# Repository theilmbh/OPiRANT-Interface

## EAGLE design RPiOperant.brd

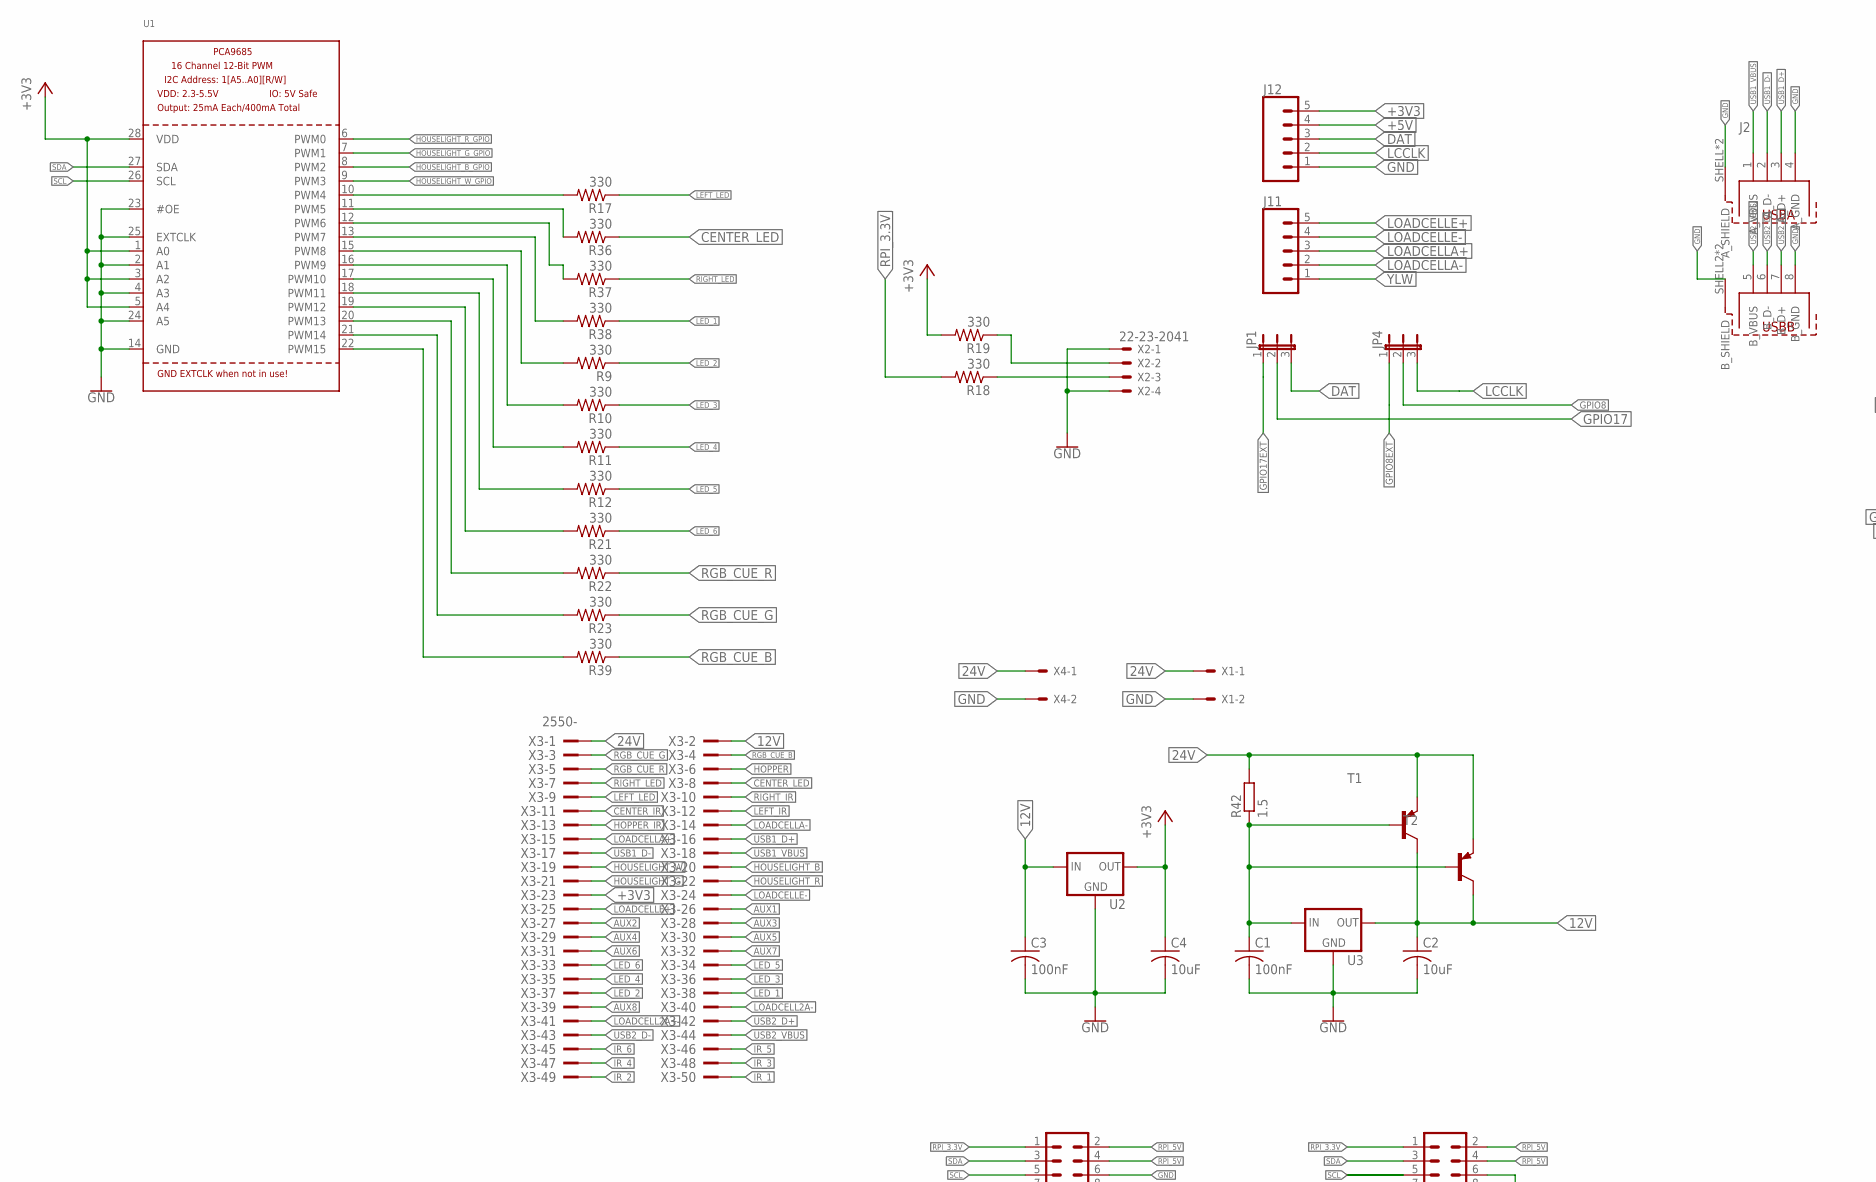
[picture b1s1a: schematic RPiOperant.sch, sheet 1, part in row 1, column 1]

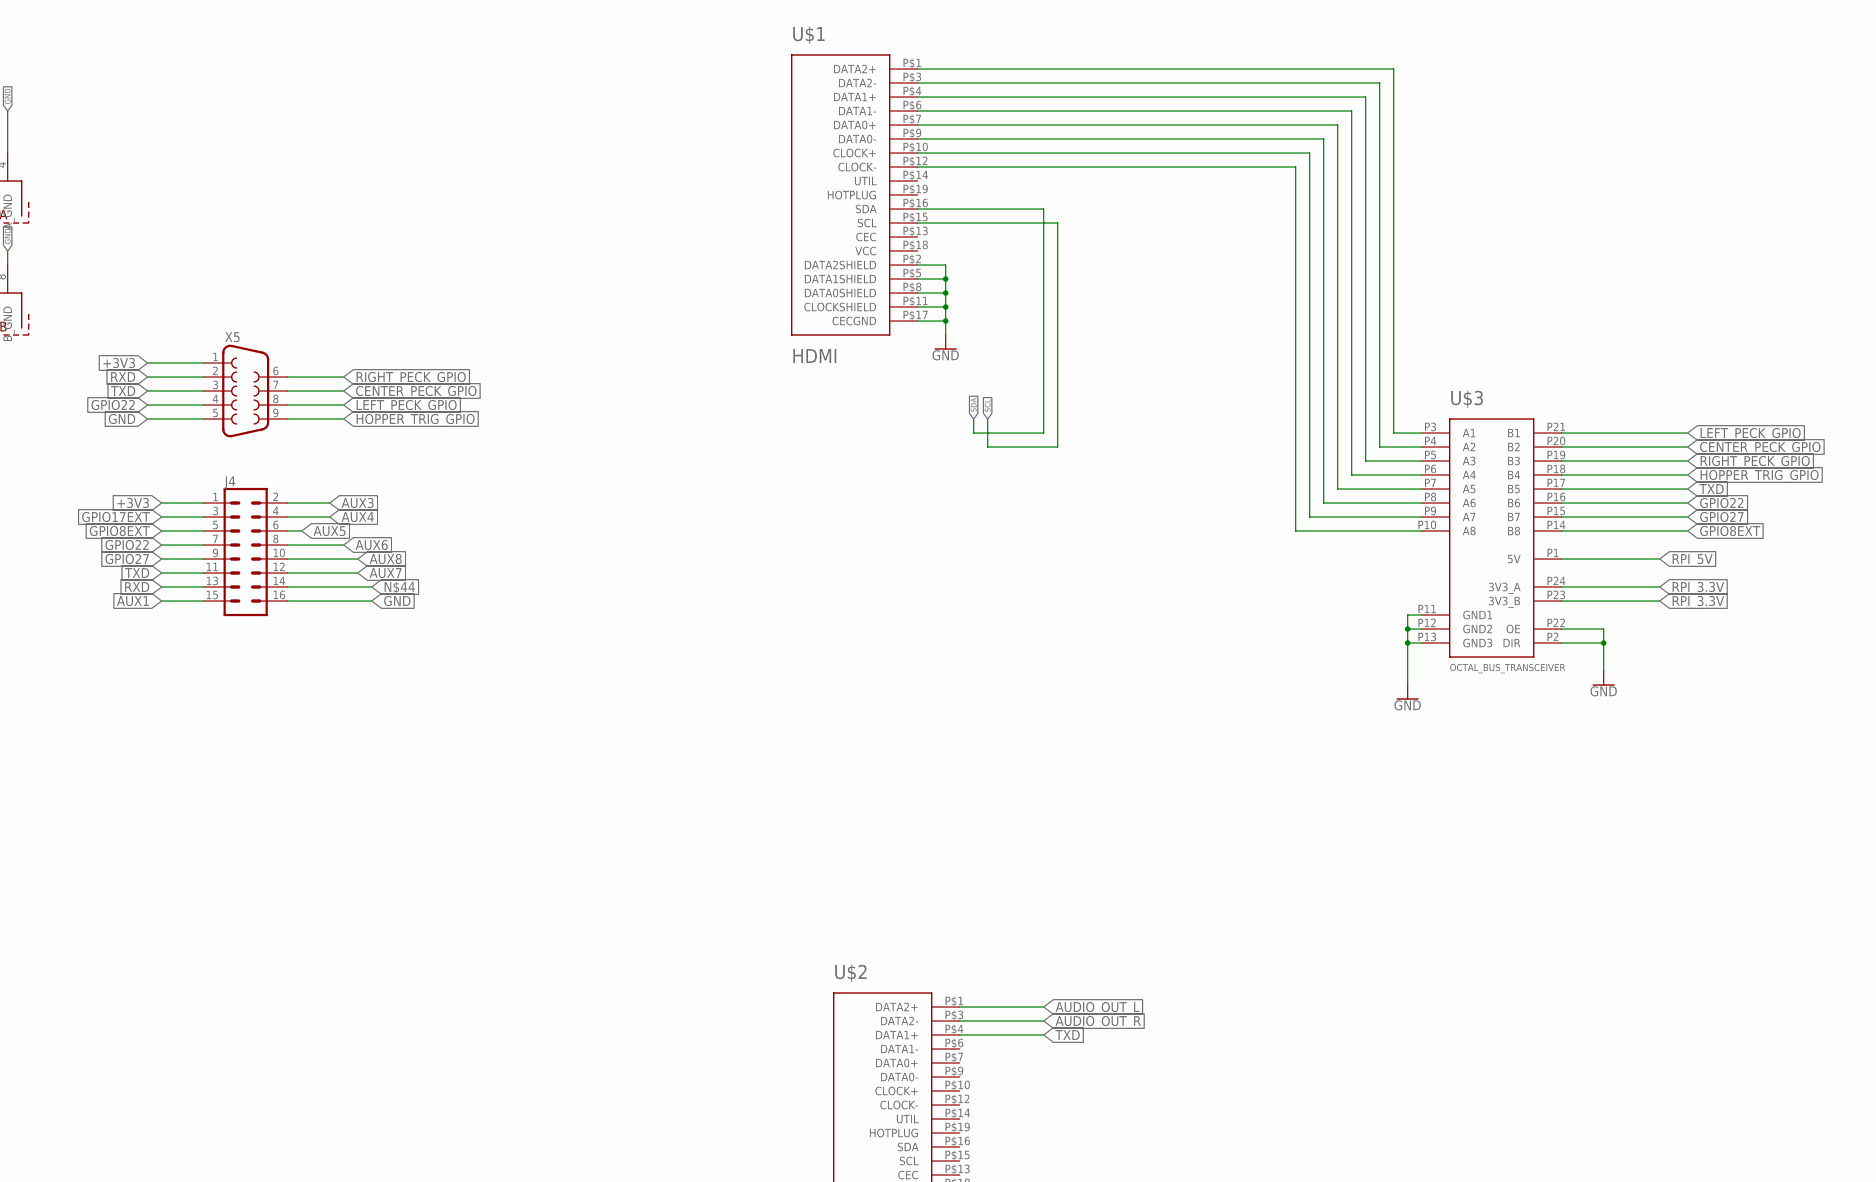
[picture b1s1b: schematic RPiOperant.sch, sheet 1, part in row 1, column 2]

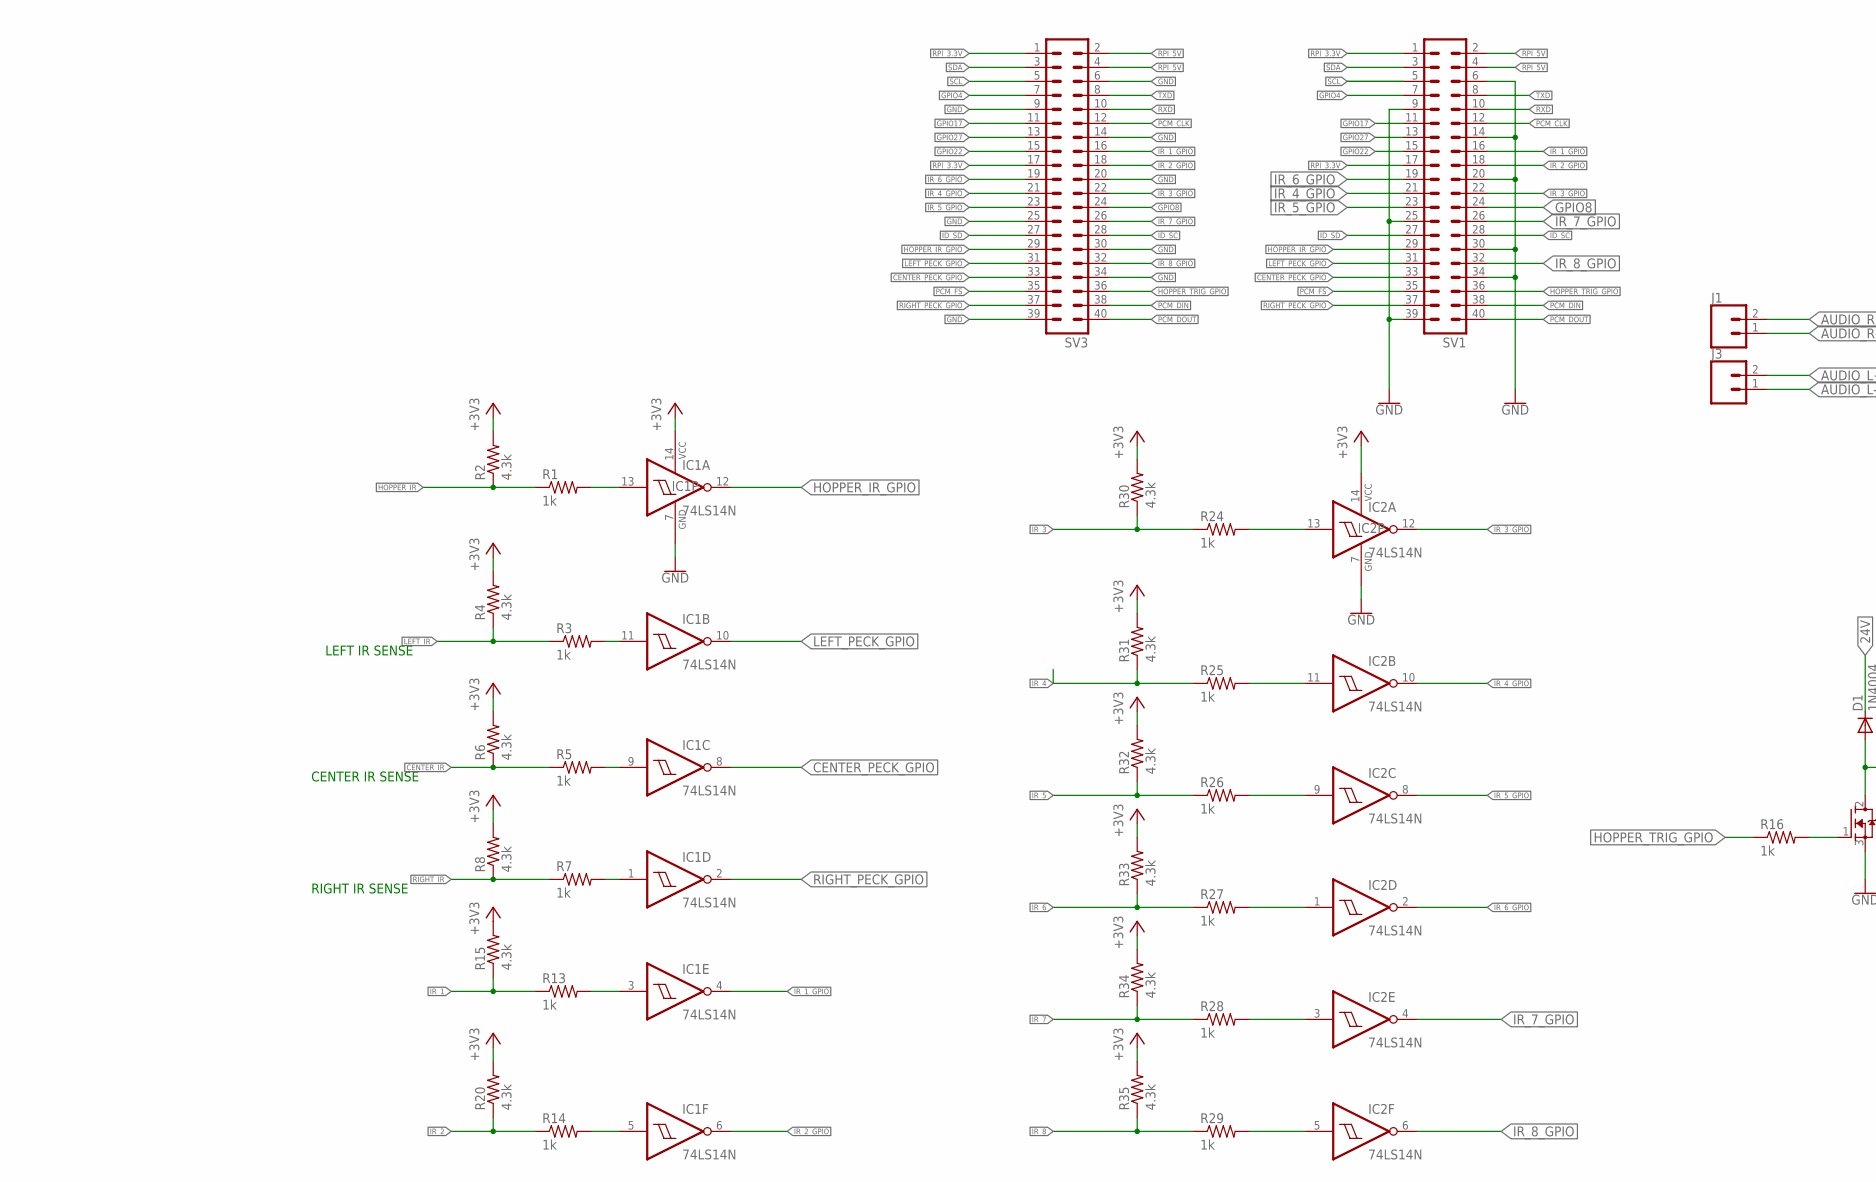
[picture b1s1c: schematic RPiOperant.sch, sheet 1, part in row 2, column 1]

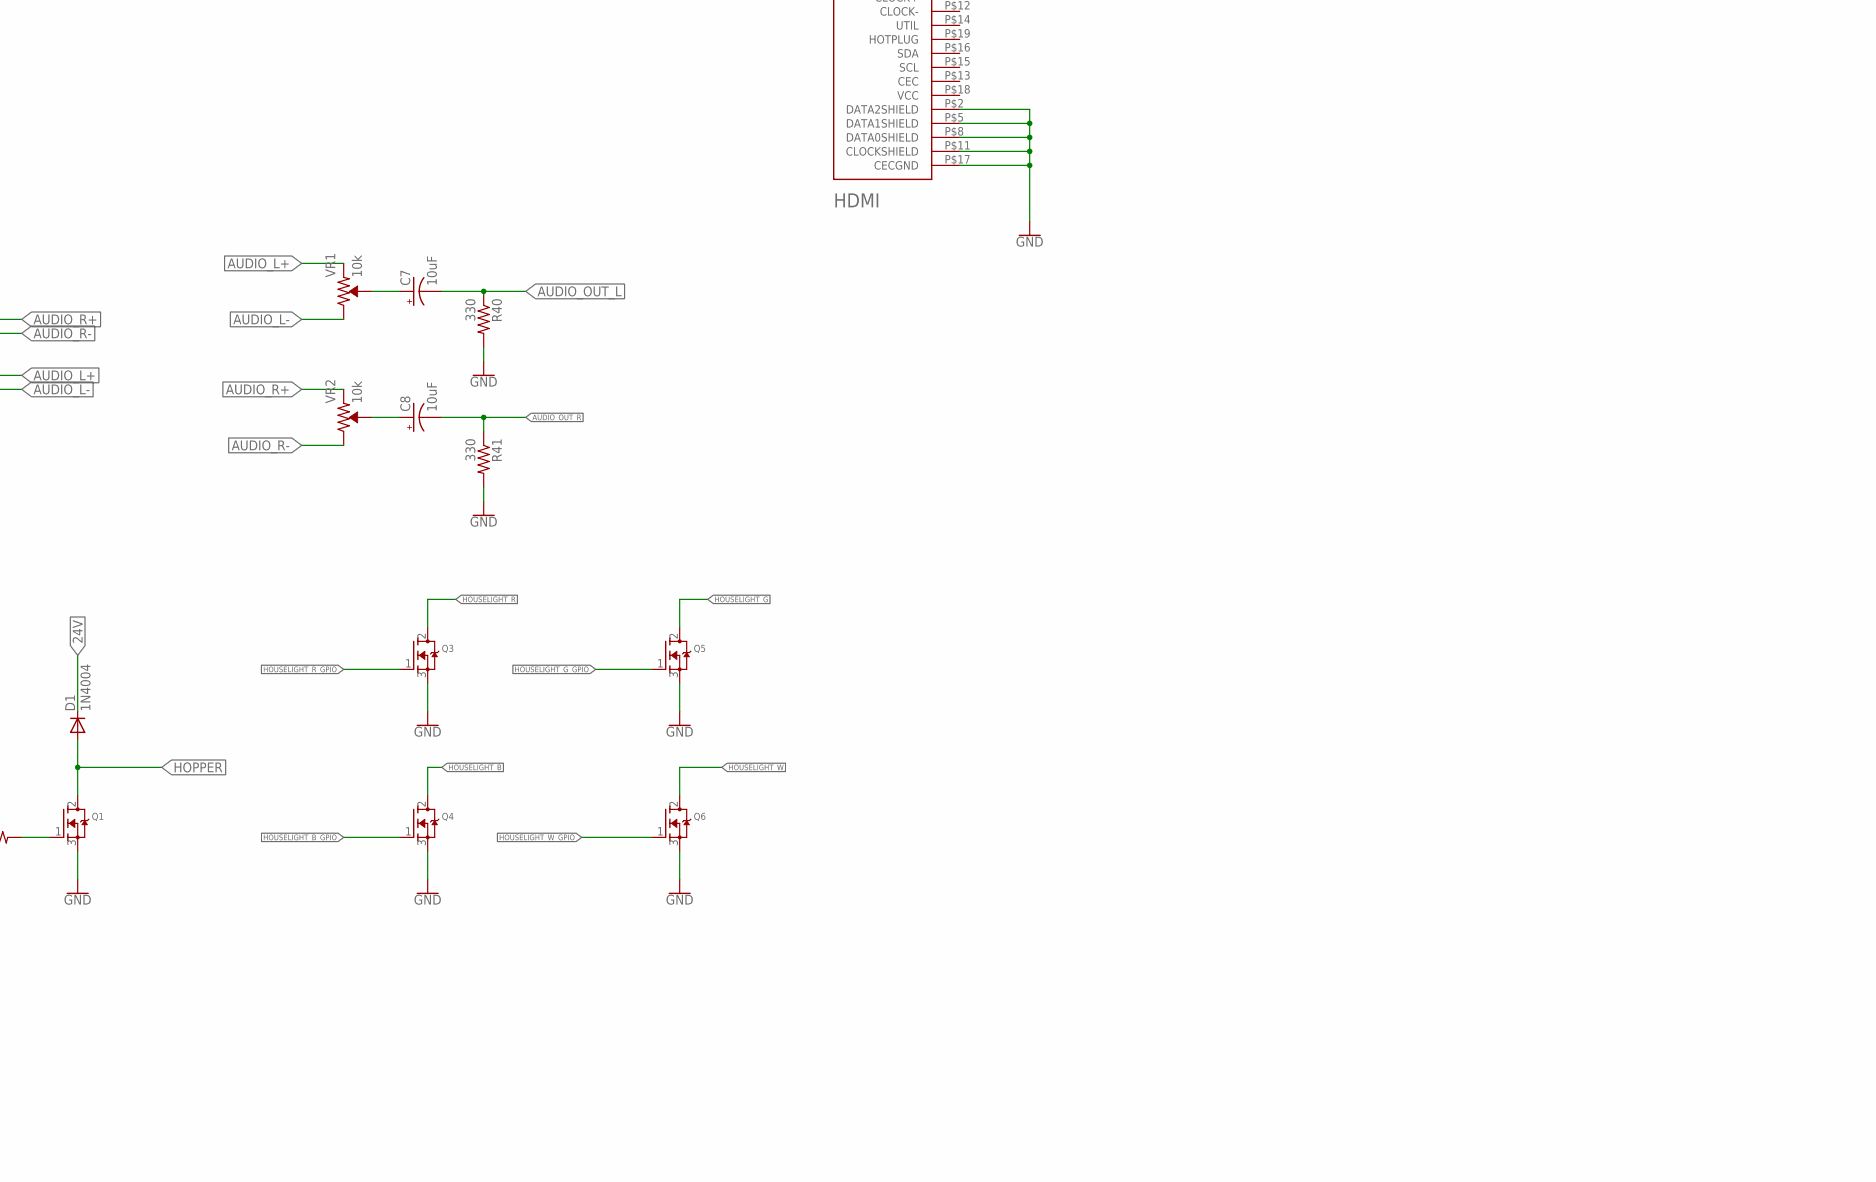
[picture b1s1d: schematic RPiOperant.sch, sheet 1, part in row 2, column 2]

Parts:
C1, C3: 100nF; C050-025X075
C2, C4: 10uF; C050-025X075
C7, C8: 10uF; CPOL-RADIAL-2.5MM-5MM
D1: 1N4004; DO41-10
IC1, IC2: 74LS14N; DIL14
J1, J3: CONN_02POLAR_LOCK; MOLEX-1X2_LOCK
J2: 61400826021
J4: CONN_08X2; 2X8
J11, J12: CONN_05; 1X05
JP1, JP4: JP2E; JP2
Q1, Q3, Q4, Q5, Q6: MOSFET-NGDS_TO220V; TO220V
R1, R3, R5, R7, R13, R14, R16, R24, R25, R26, R27, R28, R29: 1k; 0207/7
R2, R4, R6, R8, R15, R20, R30, R31, R32, R33, R34, R35: 4.3k; 0207/7
R9, R10, R11, R12, R17, R18, R19, R21, R22, R23, R36, R37, R38, R39, R40, R41: 330; 0207/7
R42: 1.5; 0411/15
SV1, SV3: MA20-2
T1, T2: -PNP-TO220V; TO220V
U1: PCA9685; TSSOP28
U2, U3: V_REG_78XXSINK; TO220-IGO
U$1, U$2: HDMI; HDMI_A
U$3: OCTAL_BUS_TRANSCEIVER; TSSOP-24
VR1, VR2: 10k; TRIMPOT-PTH-3386U
X1, X4: KK-156-2
X2: 22-23-2041
X3: 2550-; PAK100/2500-50
X5: F09HP

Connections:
12V: C2.1, C3.1, T1.2 (C), T2.2 (C), U2.IN, U3.OUT, X3.2
24V: D1.C, R42.2, T1.3 (E), T2.3 (E), X1.1, X3.1, X4.1
+3V3: C4.1, IC1.14 (VCC), IC2.14 (VCC), J4.1, J12.5, R2.2, R4.2, R6.2, R8.2, R15.2, R19.2, R20.2, R30.2, R31.2, R32.2, R33.2, R34.2, R35.2, U1.1 (A0), U1.3 (A2), U1.5 (A4), U1.28 (VDD), U2.OUT, X3.23, X5.1
+5V: J12.4
AUDIO_L+: J3.2, VR1.1 (CCW)
AUDIO_L-: J3.1, VR1.3 (CW)
AUDIO_OUT_L: C7.2 (-), R40.1, U$2.P$1 (DATA2+)
AUDIO_OUT_R: C8.2 (-), R41.1, U$2.P$3 (DATA2-)
AUDIO_R+: J1.2, VR2.1 (CCW)
AUDIO_R-: J1.1, VR2.3 (CW)
AUX1: J4.15, X3.26
AUX2: X3.27
AUX3: J4.2, X3.28
AUX4: J4.4, X3.29
AUX5: J4.6, X3.30
AUX6: J4.8, X3.31
AUX7: J4.12, X3.32
AUX8: J4.10, X3.39
CENTER_IR: R5.1, R6.1, X3.11
CENTER_LED: R36.1, X3.8
CENTER_PECK_GPIO: IC1.8 (O), SV1.33, SV3.33, U$3.P20 (B2), X5.7
DAT: J12.3, JP1.3
GND: C1.2, C2.2, C3.2, C4.2, IC1.7 (GND), IC2.7 (GND), J2.4 (A_GND), J2.8 (B_GND), J2.SHELL (A_SHIELD), J2.SHELL1 (A_SHIELD), J2.SHELL2 (B_SHIELD), J2.SHELL3 (B_SHIELD), J4.16, J12.1, Q1.3 (S), Q3.3 (S), Q4.3 (S), Q5.3 (S), Q6.3 (S), R40.2, R41.2, SV1.6, SV1.9, SV1.14, SV1.20, SV1.25, SV1.30, SV1.34, SV1.39, SV3.6, SV3.9, SV3.14, SV3.20, SV3.25, SV3.30, SV3.34, SV3.39, U1.2 (A1), U1.4 (A3), U1.14 (GND), U1.23 (#OE), U1.24 (A5), U1.25 (EXTCLK), U2.GND, U3.GND, U$1.P$2 (DATA2SHIELD), U$1.P$5 (DATA1SHIELD), U$1.P$8 (DATA0SHIELD), U$1.P$11 (CLOCKSHIELD), U$1.P$17 (CECGND), U$2.P$2 (DATA2SHIELD), U$2.P$5 (DATA1SHIELD), U$2.P$8 (DATA0SHIELD), U$2.P$11 (CLOCKSHIELD), U$2.P$17 (CECGND), U$3.P2 (DIR), U$3.P11 (GND1), U$3.P12 (GND2), U$3.P13 (GND3), U$3.P22 (OE), X1.2, X2.1, X2.4, X4.2, X5.5
GPIO4: SV1.7, SV3.7
GPIO8: JP4.2, SV1.24, SV3.24
GPIO8EXT: J4.5, JP4.1, U$3.P14 (B8)
GPIO17: JP1.2, SV1.11, SV3.11
GPIO17EXT: J4.3, JP1.1
GPIO22: J4.7, SV1.15, SV3.15, U$3.P16 (B6), X5.4
GPIO27: J4.9, SV1.13, SV3.13, U$3.P15 (B7)
HOPPER: D1.A, Q1.2 (D), X3.6
HOPPER_IR: R1.1, R2.1, X3.13
HOPPER_IR_GPIO: IC1.12 (O), SV1.29, SV3.29
HOPPER_TRIG_GPIO: R16.1, SV1.36, SV3.36, U$3.P18 (B4), X5.9
HOUSELIGHT_B: Q4.2 (D), X3.20
HOUSELIGHT_B_GPIO: Q4.1 (G), U1.8 (PWM2)
HOUSELIGHT_G: Q5.2 (D), X3.21
HOUSELIGHT_G_GPIO: Q5.1 (G), U1.7 (PWM1)
HOUSELIGHT_R: Q3.2 (D), X3.22
HOUSELIGHT_R_GPIO: Q3.1 (G), U1.6 (PWM0)
HOUSELIGHT_W: Q6.2 (D), X3.19
HOUSELIGHT_W_GPIO: Q6.1 (G), U1.9 (PWM3)
ID_SC: SV1.28, SV3.28
ID_SD: SV1.27, SV3.27
IR_1: R13.1, R15.1, X3.50
IR_1_GPIO: IC1.4 (O), SV1.16, SV3.16
IR_2: R14.1, R20.1, X3.49
IR_2_GPIO: IC1.6 (O), SV1.18, SV3.18
IR_3: R24.1, R30.1, X3.48
IR_3_GPIO: IC2.12 (O), SV1.22, SV3.22
IR_4: R25.1, R31.1, X3.47
IR_4_GPIO: IC2.10 (O), SV1.21, SV3.21
IR_5: R26.1, R32.1, X3.46
IR_5_GPIO: IC2.8 (O), SV1.23, SV3.23
IR_6: R27.1, R33.1, X3.45
IR_6_GPIO: IC2.2 (O), SV1.19, SV3.19
IR_7: R28.1, R34.1
IR_7_GPIO: IC2.4 (O), SV1.26, SV3.26
IR_8: R29.1, R35.1
IR_8_GPIO: IC2.6 (O), SV1.32, SV3.32
LCCLK: J12.2, JP4.3
LED_1: R38.1, X3.38
LED_2: R9.1, X3.37
LED_3: R10.1, X3.36
LED_4: R11.1, X3.35
LED_5: R12.1, X3.34
LED_6: R21.1, X3.33
LEFT_IR: R3.1, R4.1, X3.12
LEFT_LED: R17.1, X3.9
LEFT_PECK_GPIO: IC1.10 (O), SV1.31, SV3.31, U$3.P21 (B1), X5.8
LOADCELL2A+: X3.41
LOADCELL2A-: X3.40
LOADCELLA+: J11.3, X3.15
LOADCELLA-: J11.2, X3.14
LOADCELLE+: J11.5, X3.25
LOADCELLE-: J11.4, X3.24
unnamed: IC1.3 (I), R13.2
unnamed: IC1.5 (I), R14.2
unnamed: IC2.13 (I), R24.2
unnamed: IC2.11 (I), R25.2
unnamed: IC2.9 (I), R26.2
unnamed: IC1.13 (I), R1.2
unnamed: IC2.1 (I), R27.2
unnamed: IC1.11 (I), R3.2
unnamed: IC2.3 (I), R28.2
unnamed: IC1.9 (I), R5.2
unnamed: IC2.5 (I), R29.2
unnamed: IC1.1 (I), R7.2
unnamed: R17.2, U1.10 (PWM4)
unnamed: R36.2, U1.11 (PWM5)
unnamed: R37.2, U1.12 (PWM6)
unnamed: R38.2, U1.13 (PWM7)
unnamed: U$1.P$1 (DATA2+), U$3.P3 (A1)
unnamed: U$1.P$3 (DATA2-), U$3.P4 (A2)
unnamed: R22.2, U1.20 (PWM13)
unnamed: R23.2, U1.21 (PWM14)
unnamed: R39.2, U1.22 (PWM15)
unnamed: C1.1, R42.1, T1.1 (B), T2.1 (B), U3.IN
unnamed: Q1.1 (G), R16.2
unnamed: R19.1, X2.2
unnamed: R9.2, U1.15 (PWM8)
unnamed: R10.2, U1.16 (PWM9)
unnamed: R11.2, U1.17 (PWM10)
unnamed: R12.2, U1.18 (PWM11)
unnamed: R21.2, U1.19 (PWM12)
unnamed: R18.1, X2.3
unnamed: U$1.P$4 (DATA1+), U$3.P5 (A3)
unnamed: U$1.P$6 (DATA1-), U$3.P6 (A4)
unnamed: C7.1 (+), VR1.2 (WIPER)
unnamed: C8.1 (+), VR2.2 (WIPER)
unnamed: U$1.P$7 (DATA0+), U$3.P7 (A5)
unnamed: U$1.P$9 (DATA0-), U$3.P8 (A6)
unnamed: U$1.P$10 (CLOCK+), U$3.P9 (A7)
unnamed: U$1.P$12 (CLOCK-), U$3.P10 (A8)
PCM_CLK: SV1.12, SV3.12
PCM_DIN: SV1.38, SV3.38
PCM_DOUT: SV1.40, SV3.40
PCM_FS: SV1.35, SV3.35
RGB_CUE_B: R39.1, X3.4
RGB_CUE_G: R23.1, X3.3
RGB_CUE_R: R22.1, X3.5
RIGHT_IR: R7.1, R8.1, X3.10
RIGHT_LED: R37.1, X3.7
RIGHT_PECK_GPIO: IC1.2 (O), SV1.37, SV3.37, U$3.P19 (B3), X5.6
RPI_3.3V: R18.2, SV1.1, SV1.17, SV3.1, SV3.17, U$3.P23 (3V3_B), U$3.P24 (3V3_A)
RPI_5V: SV1.2, SV1.4, SV3.2, SV3.4, U$3.P1 (5V)
RXD: J4.13, SV1.10, SV3.10, X5.2
SCL: SV1.5, SV3.5, U1.26 (SCL), U$1.P$15 (SCL)
SDA: SV1.3, SV3.3, U1.27 (SDA), U$1.P$16 (SDA)
TXD: J4.11, SV1.8, SV3.8, U$2.P$4 (DATA1+), U$3.P17 (B5), X5.3
USB1_D+: J2.3 (A_D+), X3.16
USB1_D-: J2.2 (A_D-), X3.17
USB1_VBUS: J2.1 (A_VBUS), X3.18
USB2_D+: J2.7 (B_D+), X3.42
USB2_D-: J2.6 (B_D-), X3.43
USB2_VBUS: J2.5 (B_VBUS), X3.44
YLW: J11.1

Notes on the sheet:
LEFT IR SENSE
CENTER IR SENSE
RIGHT IR SENSE

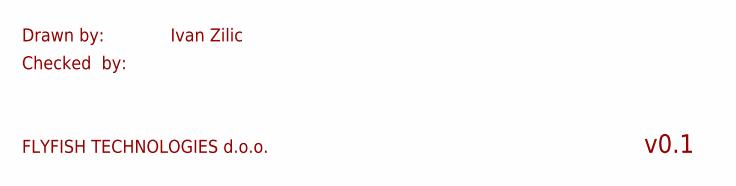
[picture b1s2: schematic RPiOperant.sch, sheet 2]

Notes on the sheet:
Drawn by:
Checked by:
FLYFISH TECHNOLOGIES d.o.o.
Ivan Zilic
v0.1

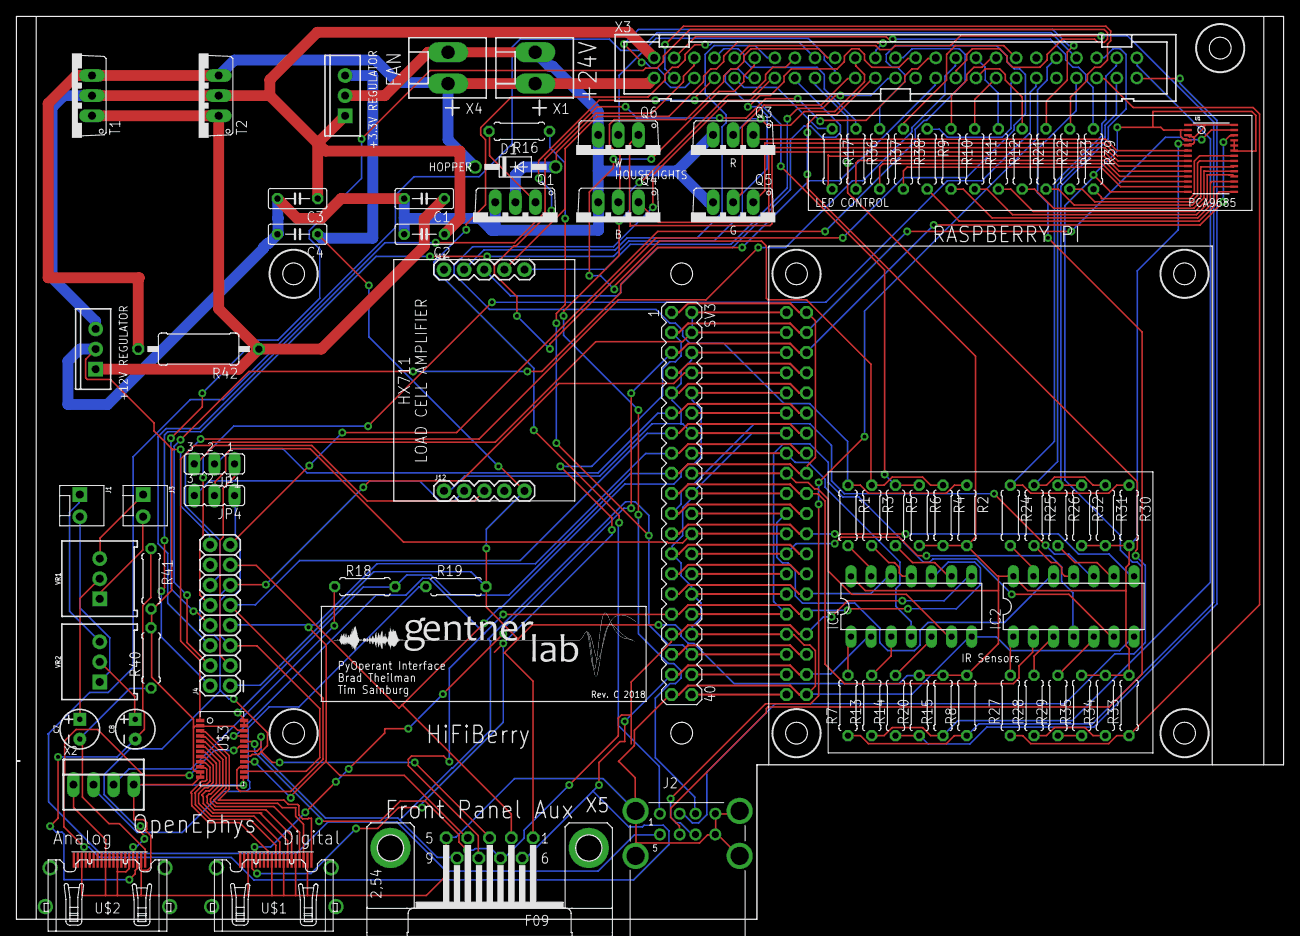
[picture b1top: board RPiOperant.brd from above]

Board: 2 copper layers, 160.0 x 114.0 mm, 81 parts (1 on the bottom side), 132 nets.

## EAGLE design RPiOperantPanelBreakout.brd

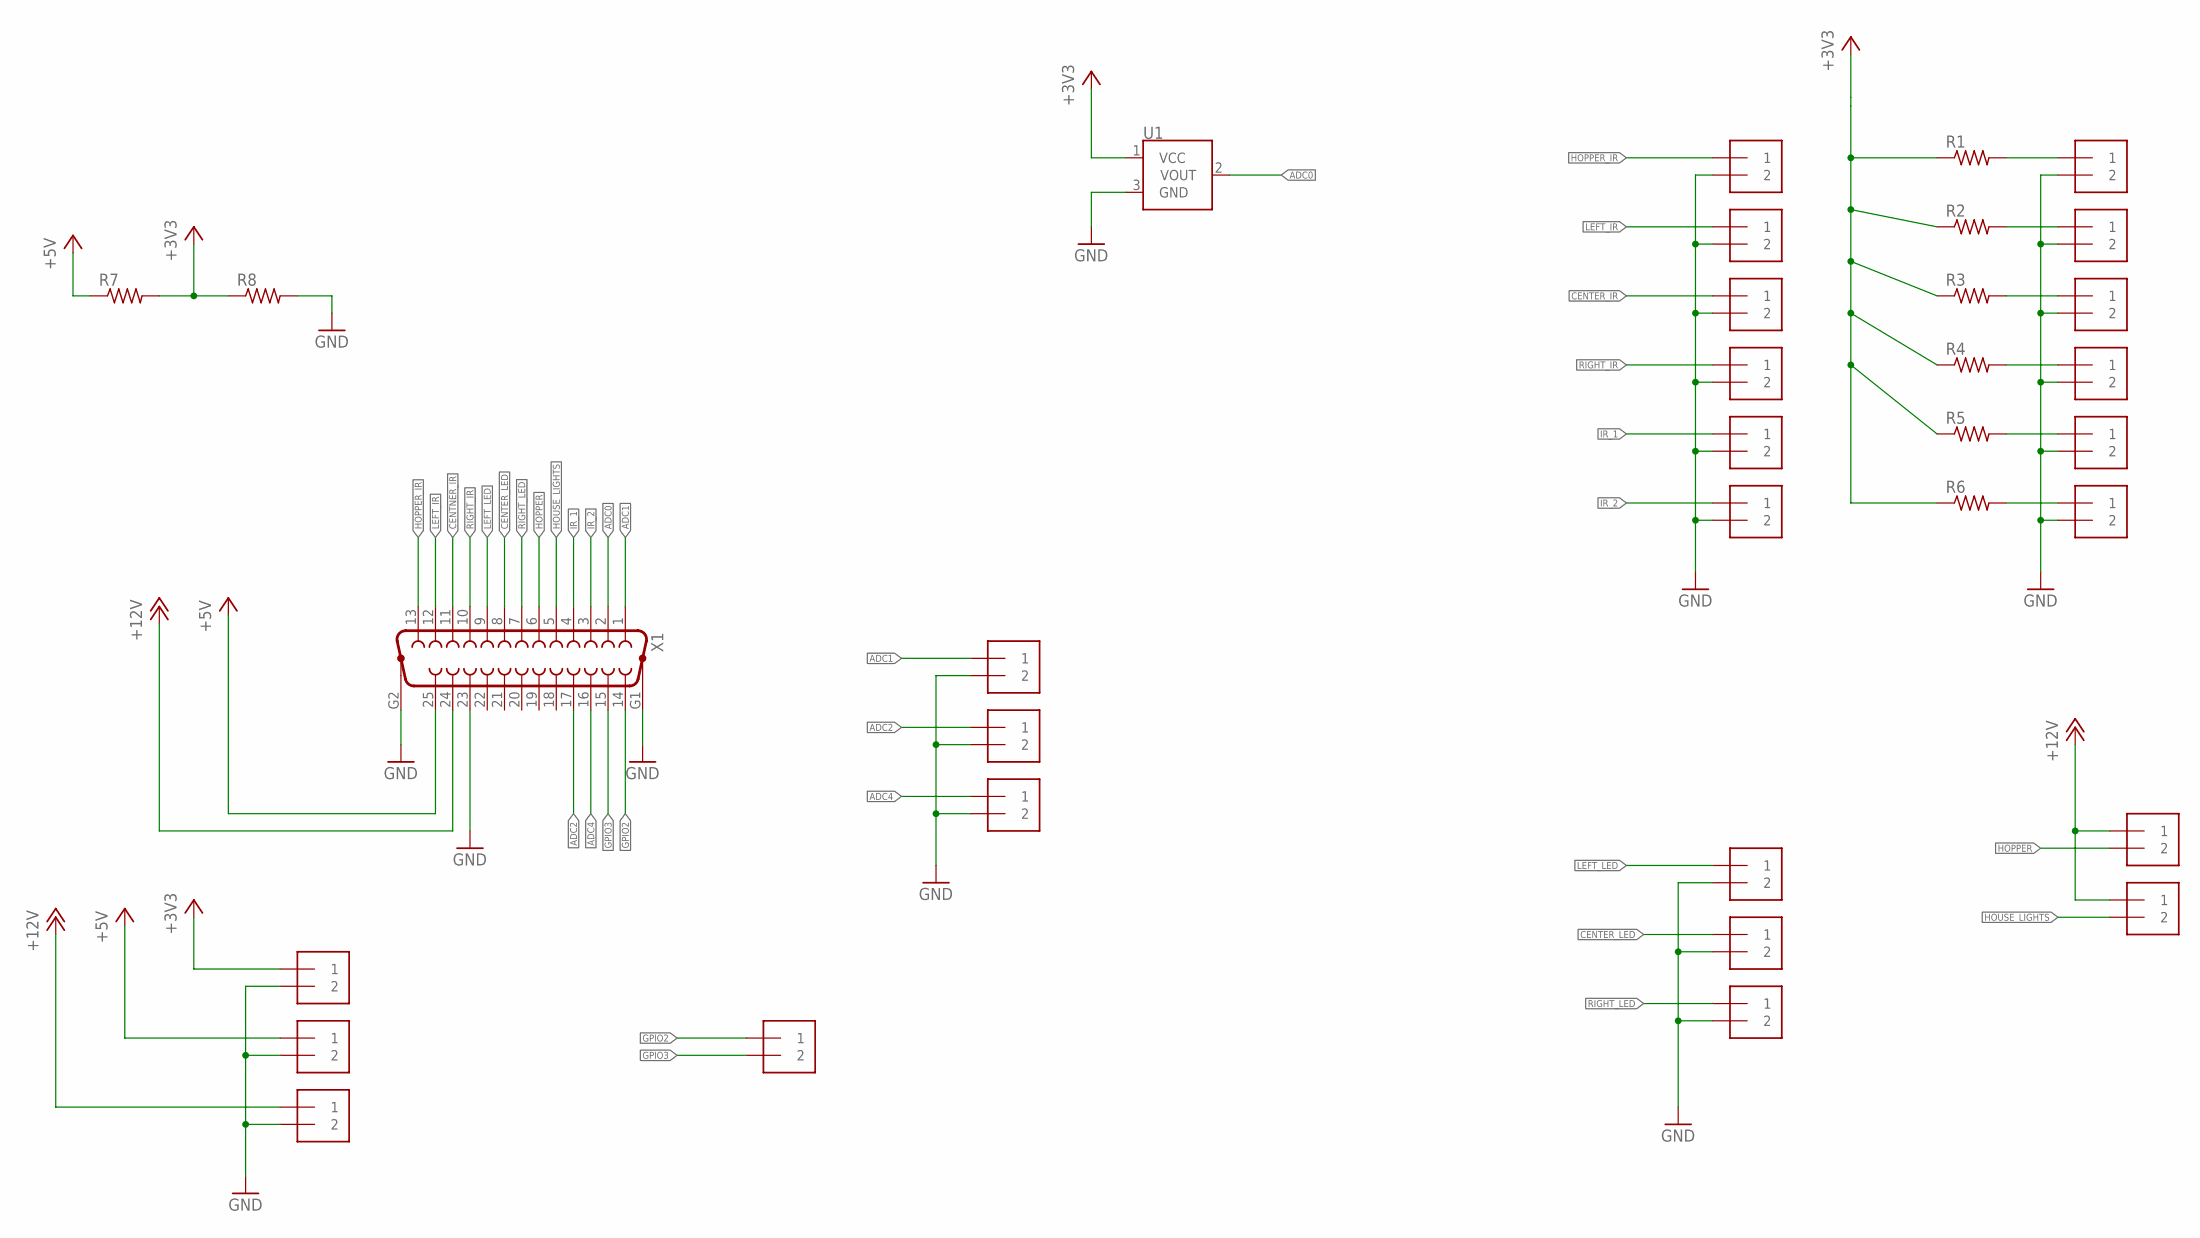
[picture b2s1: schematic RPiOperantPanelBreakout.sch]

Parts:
J1, J2, J3, J4, J5, J6, J7, J8, J9, J10, J11, J12, J13, J14, J15, J16, J17, J18, J19, J20, J21, J22, J23, J24: 1X2-3.5MM
R1, R2, R3, R4, R5, R6, R7, R8: R-US_0207/7; 0207/7
U1: TMP36GT9; TO-92
X1: F25HP

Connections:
+3V3: J18.1, R1.1, R2.1, R3.1, R4.1, R5.1, R6.1, R7.2, R8.1, U1.1 (VCC)
+5V: J19.1, R7.1, X1.25
+12V: J7.1, J8.1, J20.1, X1.24
ADC0: U1.2 (VOUT), X1.2
ADC1: J21.1, X1.1
ADC2: J23.1, X1.17
ADC4: J24.1, X1.16
CENTER_IR: J3.1
CENTER_LED: J10.1, X1.8
CENTNER_IR: X1.11
GND: J1.2, J2.2, J3.2, J4.2, J5.2, J6.2, J9.2, J10.2, J11.2, J12.2, J13.2, J14.2, J15.2, J16.2, J17.2, J18.2, J19.2, J20.2, J21.2, J23.2, J24.2, R8.2, U1.3 (GND), X1.23, X1.G1, X1.G2
GPIO2: J22.1, X1.14
GPIO3: J22.2, X1.15
HOPPER: J7.2, X1.6
HOPPER_IR: J1.1, X1.13
HOUSE_LIGHTS: J8.2, X1.5
IR_1: J5.1, X1.4
IR_2: J6.1, X1.3
LEFT_IR: J2.1, X1.12
LEFT_LED: J9.1, X1.9
unnamed: J13.1, R2.2
unnamed: J15.1, R4.2
unnamed: J12.1, R1.2
unnamed: J14.1, R3.2
unnamed: J16.1, R5.2
unnamed: J17.1, R6.2
RIGHT_IR: J4.1, X1.10
RIGHT_LED: J11.1, X1.7

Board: 2 copper layers, 34 parts (0 on the bottom side), 26 nets, no tracks yet.

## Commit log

2017-11-18 update ground plane
2017-11-20 update traces
2017-11-21 added symbolic links
2017-11-21 rework
2017-11-21 new board
2017-11-27 panel breakeout :
2017-12-11 new schematic
2017-12-11 board labesl
2017-12-14 new stuff!
2017-12-15 final draft
2017-12-15 alternate
2018-01-10 Revision A
2018-01-10 revision b
2018-01-19 version 2
2018-02-08 rev b changes... new DB25 pinout
2018-02-09 new board layout
2018-02-09 revb revisions
2018-02-13 new board!
2018-02-21 rev_b layout
2018-05-14 revb
2018-05-29 rev_c v1
2018-06-07 rev c updates
2018-06-11 revision C
2018-08-13 rev_c
2018-09-05 rev d
2018-09-08 front panel modifications

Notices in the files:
parts and their libraries:
SparkFun-Connectors: Licensing: Creative Commons ShareAlike 4.0 International - https://creativecommons.org/licenses/by-sa/4.0
InputOutputIO: Copyright: Würth Elektronik
